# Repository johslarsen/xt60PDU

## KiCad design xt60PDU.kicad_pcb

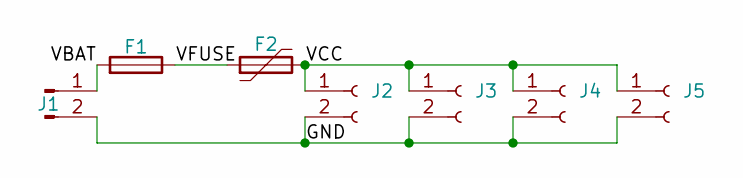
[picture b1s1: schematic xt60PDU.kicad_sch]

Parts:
F1: Fuse; Fuseholder_Littelfuse_Nano2_154x
F2: Polyfuse; SolderJumper-2_1812_Bridged_3.2mm
J1: Conn_01x02_Pin; AMASS_XT60PW-M_1x02_P7.20mm_Horizontal
J2, J3, J4, J5: Conn_01x02_Socket; AMASS_XT60-F_1x02_P7.20mm_Vertical

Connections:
/GND: J1.2, J2.2, J3.2, J4.2, J5.2
/VBAT: F1.2, J1.1
/VCC: F2.2, J2.1, J3.1, J4.1, J5.1
/VFUSE: F1.1, F2.1

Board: 2 copper layers, 7 parts (2 on the bottom side), 4 nets, no tracks yet.

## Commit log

2025-05-25 Initial version
2025-05-25 Replace the 1812 PTC footprint with one that is shorted by default
2025-05-26 Added v0.1 gerbers
2025-12-31 Add v1.0 with fixed pin numbering and connector orientation
2025-12-31 Add 3D models for enclosure and a jig to orient connectors properly
    Note that these include a generated STL of the board to sanity check the
    models. If this is not generated the OpenSCAD rendering will issue a
    harmless warning like e.g.:
    WARNING: Can't open import file '../out/xt60PDU_v1.0/xt60PDU.stl'
